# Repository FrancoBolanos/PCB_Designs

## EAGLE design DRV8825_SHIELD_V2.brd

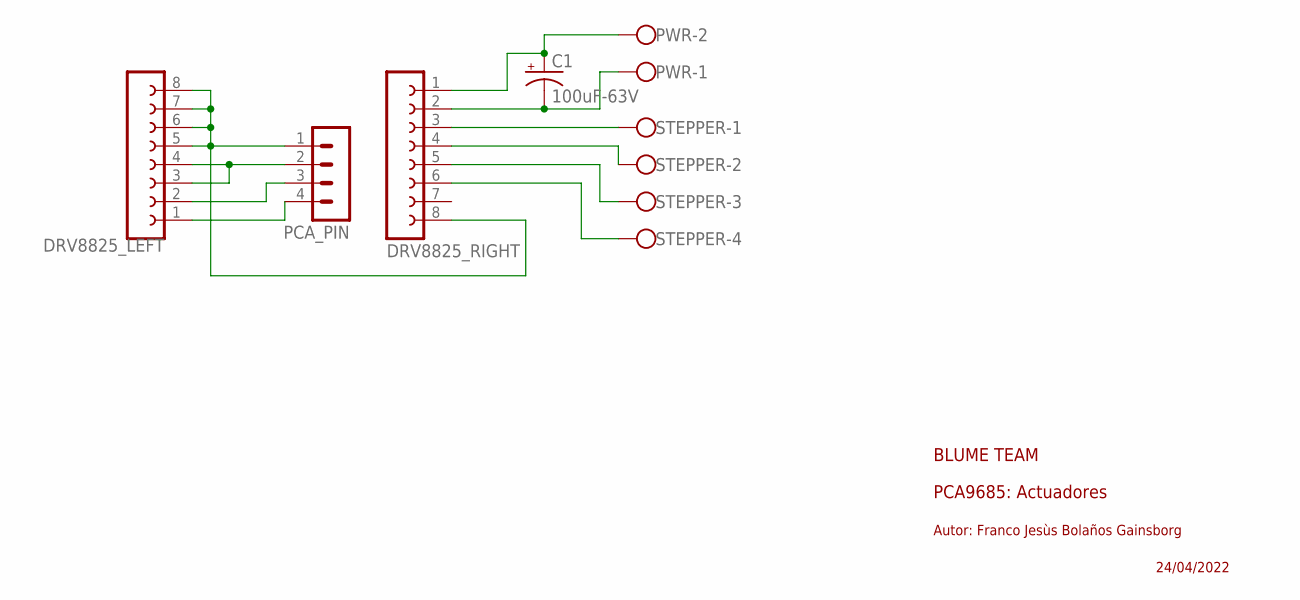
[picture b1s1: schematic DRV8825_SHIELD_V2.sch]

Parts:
C1: 100uF-63V; E5-10,5
DRV8825_LEFT, DRV8825_RIGHT: FE08-1; FE08
PCA_PIN: MA04-1
PWR: W237-102
STEPPER: W237-4

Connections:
unnamed: DRV8825_RIGHT.3, STEPPER.1
unnamed: DRV8825_RIGHT.4, STEPPER.2
unnamed: DRV8825_LEFT.1, PCA_PIN.4
unnamed: DRV8825_RIGHT.5, STEPPER.3
unnamed: C1.+, DRV8825_RIGHT.1, PWR.2
unnamed: C1.-, DRV8825_RIGHT.2, PWR.1
unnamed: DRV8825_LEFT.2, PCA_PIN.3
unnamed: DRV8825_RIGHT.6, STEPPER.4
unnamed: DRV8825_LEFT.5, DRV8825_LEFT.6, DRV8825_LEFT.7, DRV8825_LEFT.8, DRV8825_RIGHT.8, PCA_PIN.1
unnamed: DRV8825_LEFT.3, DRV8825_LEFT.4, PCA_PIN.2

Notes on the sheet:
BLUME TEAM
PCA9685: Actuadores
Autor: Franco Jesùs Bolaños Gainsborg
24/04/2022

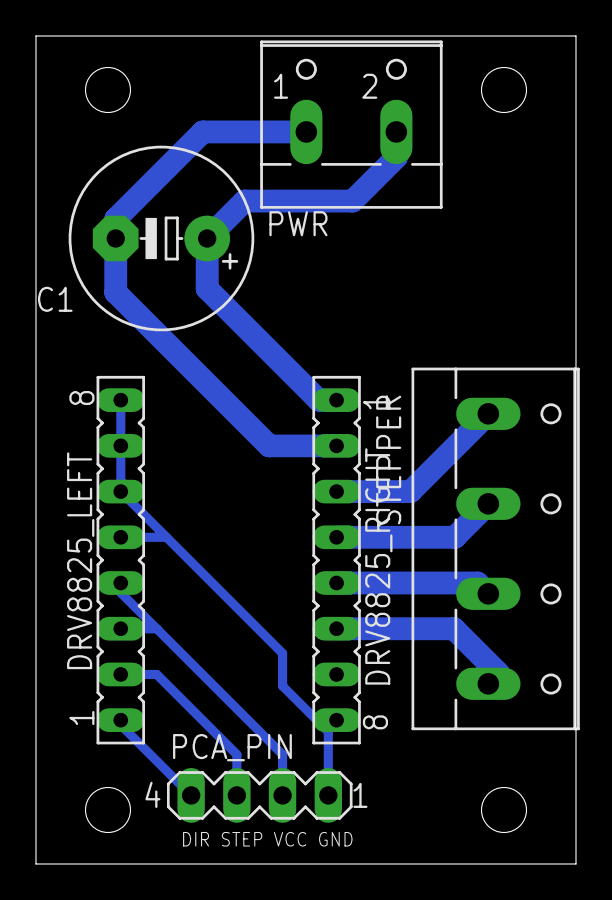
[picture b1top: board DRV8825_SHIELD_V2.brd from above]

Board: 2 copper layers, 30.0 x 46.0 mm, 6 parts (0 on the bottom side), 10 nets.

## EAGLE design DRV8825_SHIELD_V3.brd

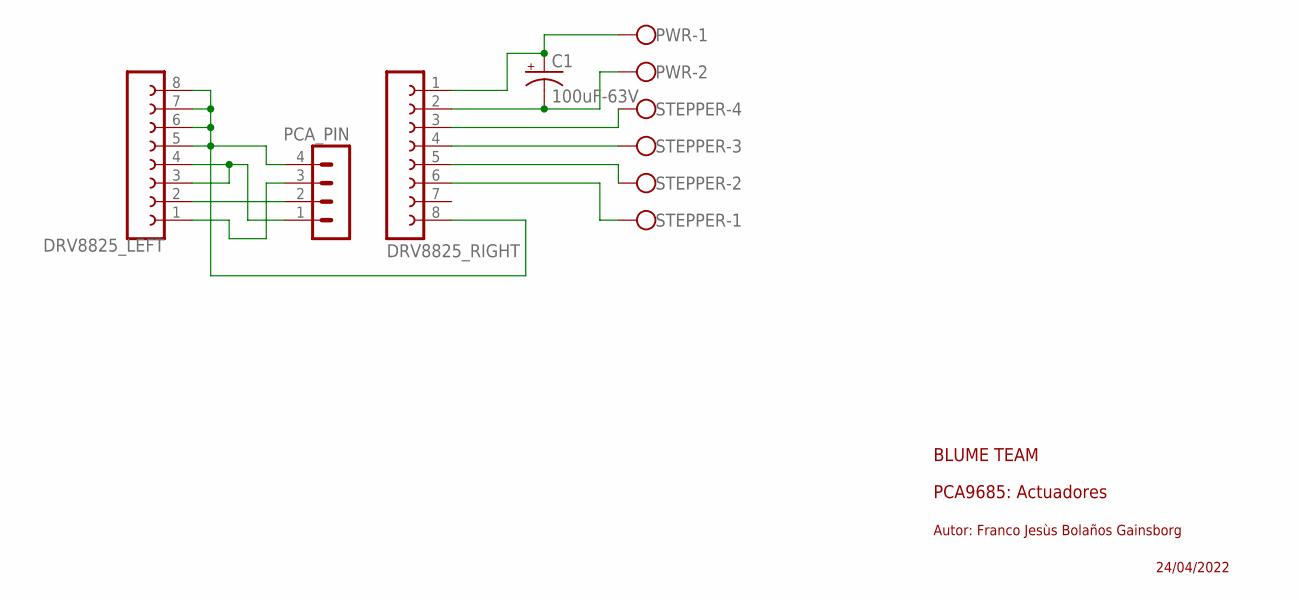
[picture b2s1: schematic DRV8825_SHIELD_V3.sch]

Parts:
C1: 100uF-63V; E5-10,5
DRV8825_LEFT, DRV8825_RIGHT: FE08-1; FE08
PCA_PIN: MA04-1
PWR: W237-102
STEPPER: W237-4

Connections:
unnamed: DRV8825_RIGHT.3, STEPPER.4
unnamed: DRV8825_RIGHT.4, STEPPER.3
unnamed: DRV8825_LEFT.2, PCA_PIN.2
unnamed: DRV8825_LEFT.1, PCA_PIN.3
unnamed: C1.+, DRV8825_RIGHT.1, PWR.1
unnamed: C1.-, DRV8825_RIGHT.2, PWR.2
unnamed: DRV8825_LEFT.3, DRV8825_LEFT.4, PCA_PIN.1
unnamed: DRV8825_RIGHT.5, STEPPER.2
unnamed: DRV8825_RIGHT.6, STEPPER.1
unnamed: DRV8825_LEFT.5, DRV8825_LEFT.6, DRV8825_LEFT.7, DRV8825_LEFT.8, DRV8825_RIGHT.8, PCA_PIN.4

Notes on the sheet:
BLUME TEAM
PCA9685: Actuadores
Autor: Franco Jesùs Bolaños Gainsborg
24/04/2022

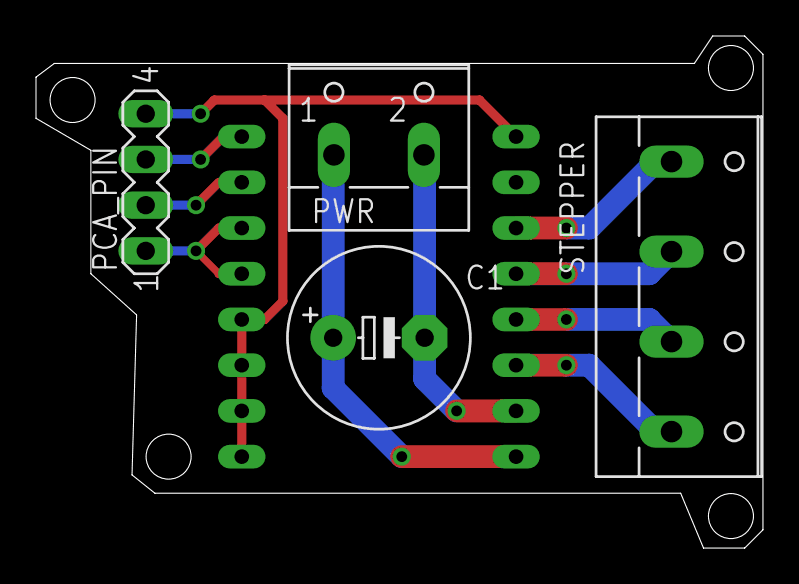
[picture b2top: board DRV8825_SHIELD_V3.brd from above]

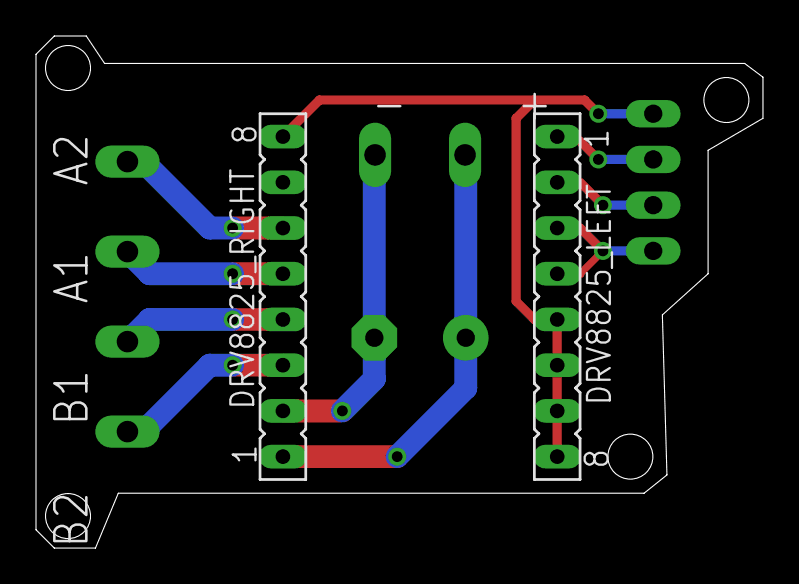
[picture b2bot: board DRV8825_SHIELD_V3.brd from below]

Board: 2 copper layers, 40.4 x 28.4 mm, 6 parts (2 on the bottom side), 10 nets.

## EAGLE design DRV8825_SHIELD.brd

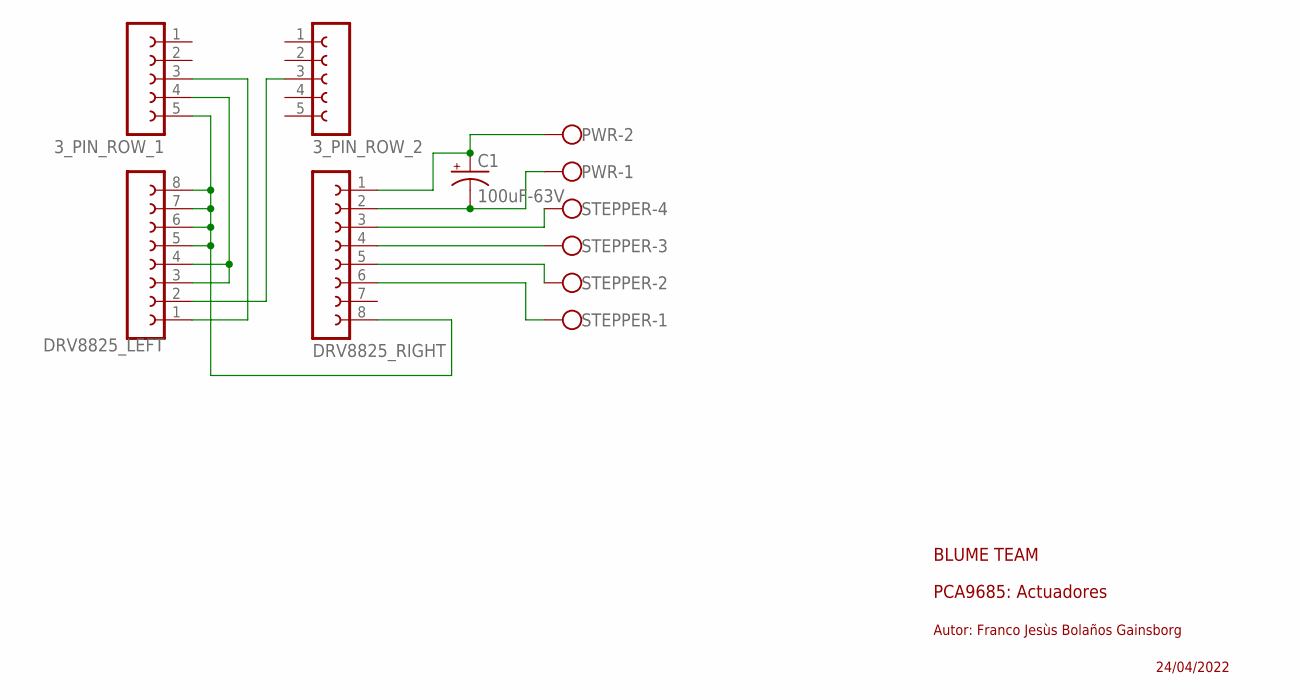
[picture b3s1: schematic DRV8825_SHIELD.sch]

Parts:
3_PIN_ROW_1, 3_PIN_ROW_2: FE05-1
C1: 100uF-63V; E5-10,5
DRV8825_LEFT, DRV8825_RIGHT: FE08-1; FE08
PWR: W237-102
STEPPER: W237-4

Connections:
unnamed: DRV8825_RIGHT.3, STEPPER.4
unnamed: 3_PIN_ROW_1.5, DRV8825_LEFT.5, DRV8825_LEFT.6, DRV8825_LEFT.7, DRV8825_LEFT.8, DRV8825_RIGHT.8
unnamed: 3_PIN_ROW_1.3, DRV8825_LEFT.1
unnamed: 3_PIN_ROW_2.3, DRV8825_LEFT.2
unnamed: C1.+, DRV8825_RIGHT.1, PWR.2
unnamed: C1.-, DRV8825_RIGHT.2, PWR.1
unnamed: DRV8825_RIGHT.4, STEPPER.3
unnamed: 3_PIN_ROW_1.4, DRV8825_LEFT.3, DRV8825_LEFT.4
unnamed: DRV8825_RIGHT.5, STEPPER.2
unnamed: DRV8825_RIGHT.6, STEPPER.1

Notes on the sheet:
BLUME TEAM
PCA9685: Actuadores
Autor: Franco Jesùs Bolaños Gainsborg
24/04/2022

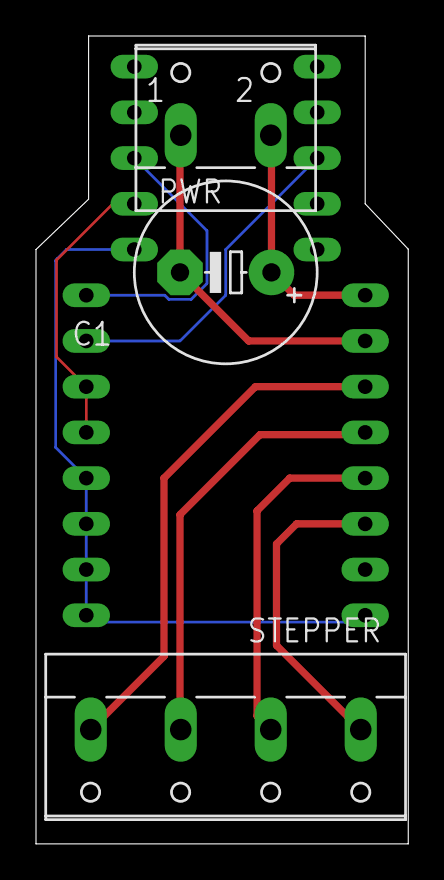
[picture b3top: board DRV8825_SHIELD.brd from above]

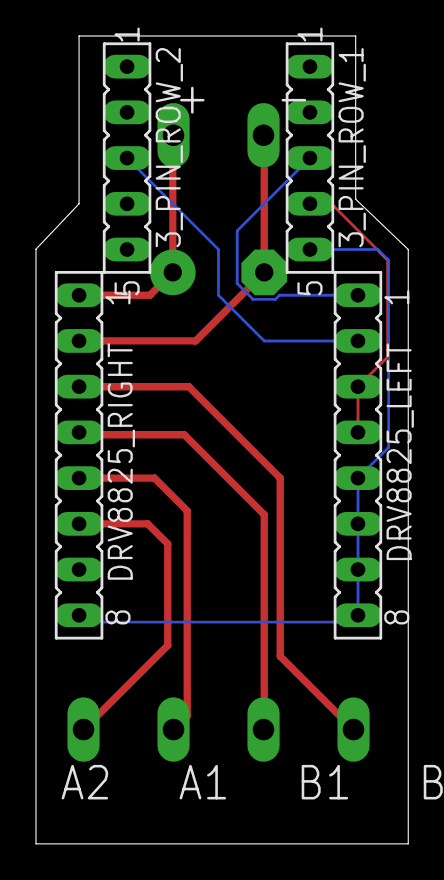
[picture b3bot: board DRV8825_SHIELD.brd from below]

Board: 2 copper layers, 20.7 x 44.9 mm, 7 parts (4 on the bottom side), 10 nets.

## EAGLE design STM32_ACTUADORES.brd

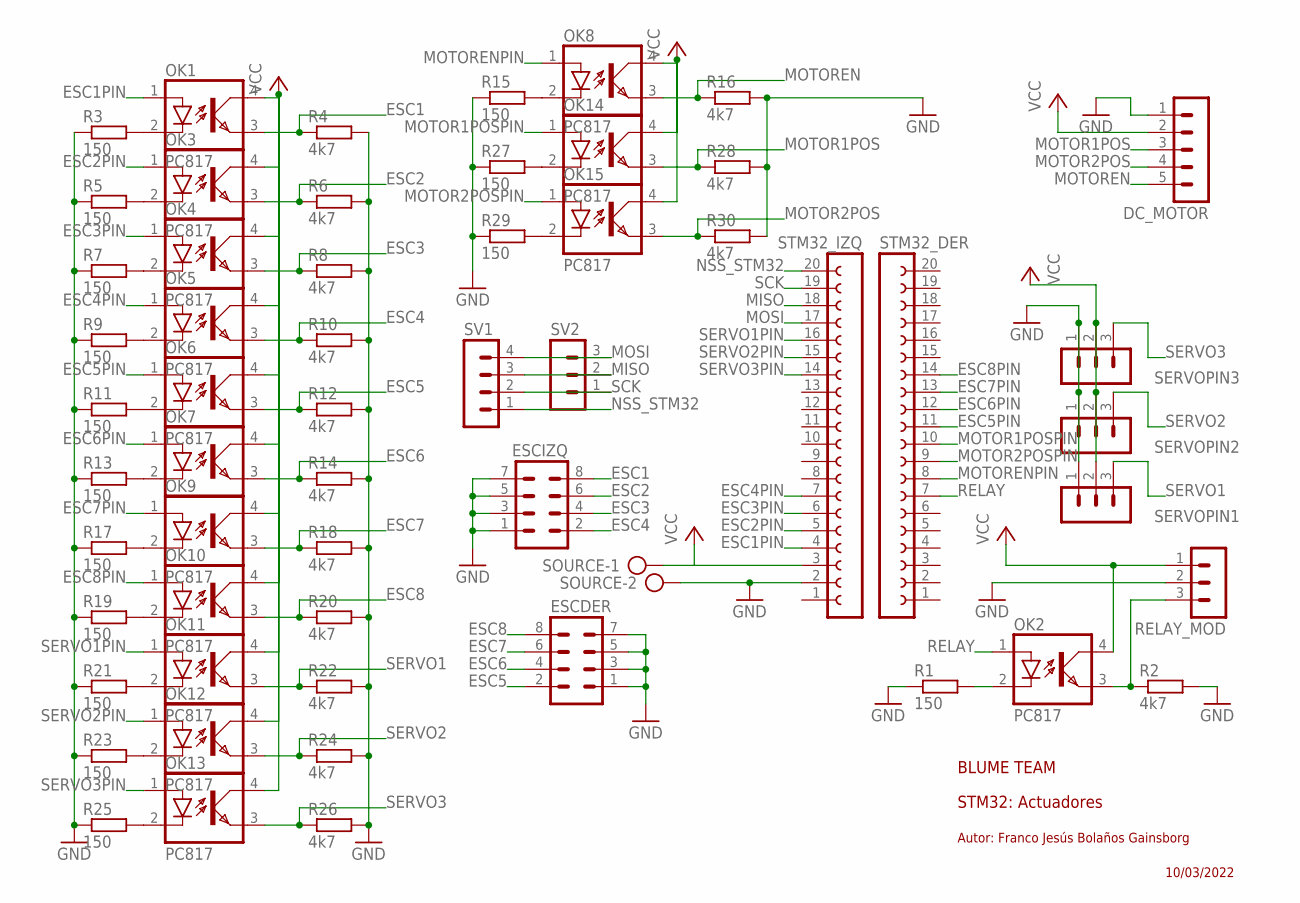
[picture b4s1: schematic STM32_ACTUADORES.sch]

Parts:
DC_MOTOR: MA05-1
ESCDER: MA04-2
ESCIZQ: MA04-2
OK1, OK2, OK3, OK4, OK5, OK6, OK7, OK8, OK9, OK10, OK11, OK12, OK13, OK14, OK15: PC817; DIL04
R1, R3, R5, R7, R9, R11, R13, R15, R17, R19, R21, R23, R25, R27, R29: 150; 0207/10
R2, R4, R6, R8, R10, R12, R14, R16, R18, R20, R22, R24, R26, R28, R30: 4k7; 0207/10
RELAY_MOD: MA03-1
SERVOPIN1, SERVOPIN2, SERVOPIN3: MA03-1
SOURCE: AK300/2
STM32_DER, STM32_IZQ: FE20-1; FE20
SV1: MA04-1
SV2: MA03-1

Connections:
ESC1: ESCIZQ.8, OK1.3 (EMIT), R4.1
ESC1PIN: OK1.1 (A), STM32_IZQ.4
ESC2: ESCIZQ.6, OK3.3 (EMIT), R6.1
ESC2PIN: OK3.1 (A), STM32_IZQ.5
ESC3: ESCIZQ.4, OK4.3 (EMIT), R8.1
ESC3PIN: OK4.1 (A), STM32_IZQ.6
ESC4: ESCIZQ.2, OK5.3 (EMIT), R10.1
ESC4PIN: OK5.1 (A), STM32_IZQ.7
ESC5: ESCDER.2, OK6.3 (EMIT), R12.1
ESC5PIN: OK6.1 (A), STM32_DER.11
ESC6: ESCDER.4, OK7.3 (EMIT), R14.1
ESC6PIN: OK7.1 (A), STM32_DER.12
ESC7: ESCDER.6, OK9.3 (EMIT), R18.1
ESC7PIN: OK9.1 (A), STM32_DER.13
ESC8: ESCDER.8, OK10.3 (EMIT), R20.1
ESC8PIN: OK10.1 (A), STM32_DER.14
GND: DC_MOTOR.1, ESCDER.1, ESCDER.3, ESCDER.5, ESCDER.7, ESCIZQ.1, ESCIZQ.3, ESCIZQ.5, ESCIZQ.7, R1.1, R2.2, R3.1, R4.2, R5.1, R6.2, R7.1, R8.2, R9.1, R10.2, R11.1, R12.2, R13.1, R14.2, R15.1, R16.2, R17.1, R18.2, R19.1, R20.2, R21.1, R22.2, R23.1, R24.2, R25.1, R26.2, R27.1, R28.2, R29.1, R30.2, RELAY_MOD.2, SERVOPIN1.1, SERVOPIN2.1, SERVOPIN3.1, SOURCE.2, STM32_IZQ.2
MISO: STM32_IZQ.18, SV1.3, SV2.2
MOSI: STM32_IZQ.17, SV1.4, SV2.3
MOTOR1POS: DC_MOTOR.3, OK14.3 (EMIT), R28.1
MOTOR1POSPIN: OK14.1 (A), STM32_DER.10
MOTOR2POS: DC_MOTOR.4, OK15.3 (EMIT), R30.1
MOTOR2POSPIN: OK15.1 (A), STM32_DER.9
MOTOREN: DC_MOTOR.5, OK8.3 (EMIT), R16.1
MOTORENPIN: OK8.1 (A), STM32_DER.8
unnamed: OK1.2 (C), R3.2
unnamed: OK2.2 (C), R1.2
unnamed: OK2.3 (EMIT), R2.1, RELAY_MOD.3
unnamed: OK8.2 (C), R15.2
unnamed: OK14.2 (C), R27.2
unnamed: OK3.2 (C), R5.2
unnamed: OK15.2 (C), R29.2
unnamed: OK13.2 (C), R25.2
unnamed: OK4.2 (C), R7.2
unnamed: OK5.2 (C), R9.2
unnamed: OK6.2 (C), R11.2
unnamed: OK7.2 (C), R13.2
unnamed: OK9.2 (C), R17.2
unnamed: OK10.2 (C), R19.2
unnamed: OK11.2 (C), R21.2
unnamed: OK12.2 (C), R23.2
NSS_STM32: STM32_IZQ.20, SV1.1
RELAY: OK2.1 (A), STM32_DER.7
SCK: STM32_IZQ.19, SV1.2, SV2.1
SERVO1: OK11.3 (EMIT), R22.1, SERVOPIN1.3
SERVO1PIN: OK11.1 (A), STM32_IZQ.16
SERVO2: OK12.3 (EMIT), R24.1, SERVOPIN2.3
SERVO2PIN: OK12.1 (A), STM32_IZQ.15
SERVO3: OK13.3 (EMIT), R26.1, SERVOPIN3.3
SERVO3PIN: OK13.1 (A), STM32_IZQ.14
VCC: DC_MOTOR.2, OK1.4 (COL), OK2.4 (COL), OK3.4 (COL), OK4.4 (COL), OK5.4 (COL), OK6.4 (COL), OK7.4 (COL), OK8.4 (COL), OK9.4 (COL), OK10.4 (COL), OK11.4 (COL), OK12.4 (COL), OK13.4 (COL), OK14.4 (COL), OK15.4 (COL), RELAY_MOD.1, SERVOPIN1.2, SERVOPIN2.2, SERVOPIN3.2, SOURCE.1, STM32_IZQ.3

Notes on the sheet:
BLUME TEAM
STM32: Actuadores
Autor: Franco Jesús Bolaños Gainsborg
10/03/2022

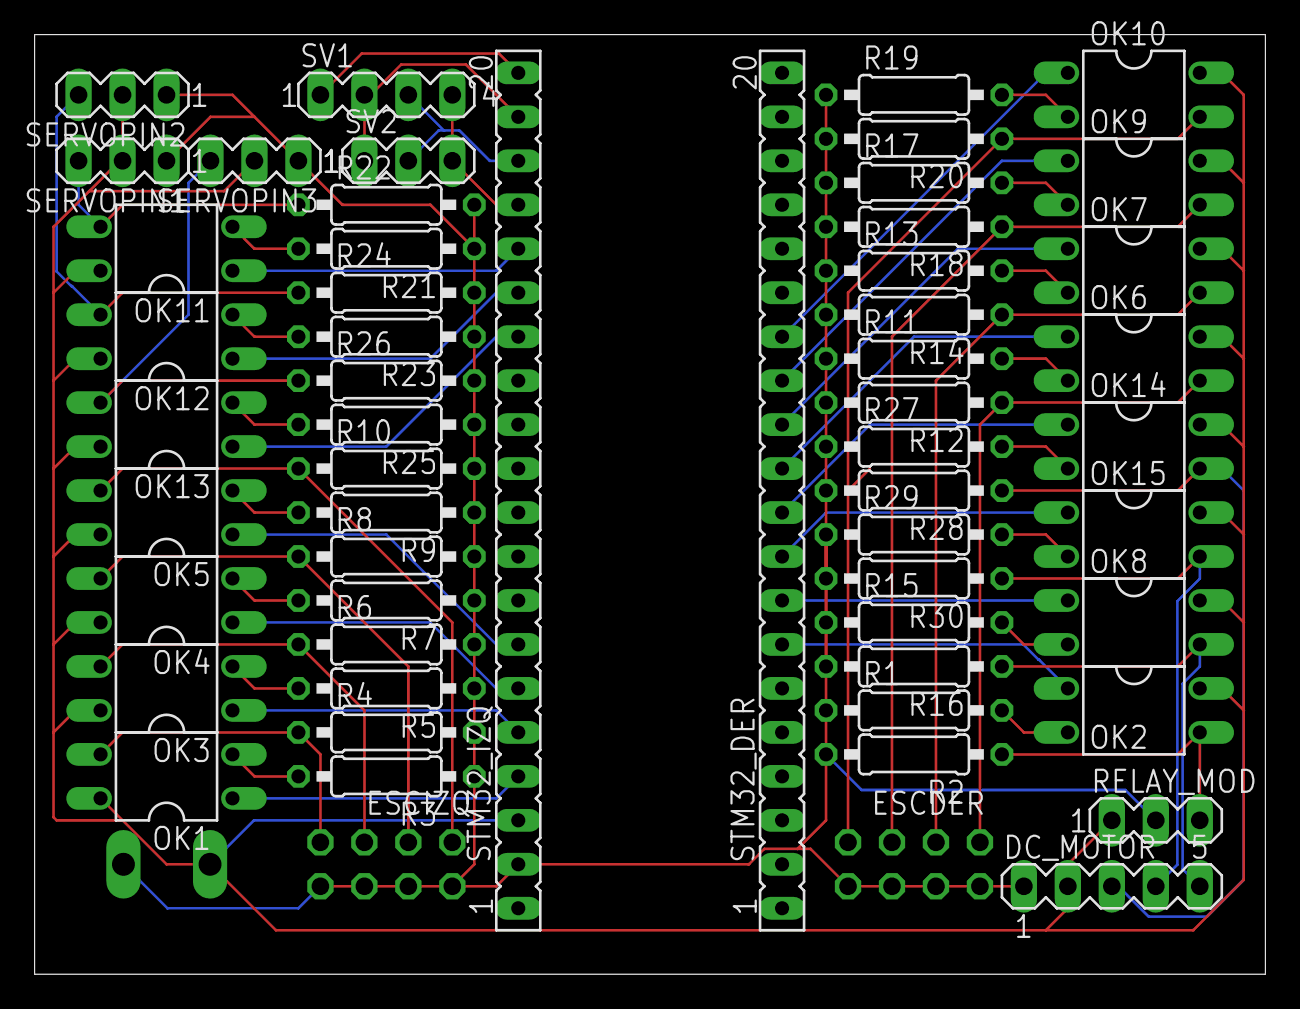
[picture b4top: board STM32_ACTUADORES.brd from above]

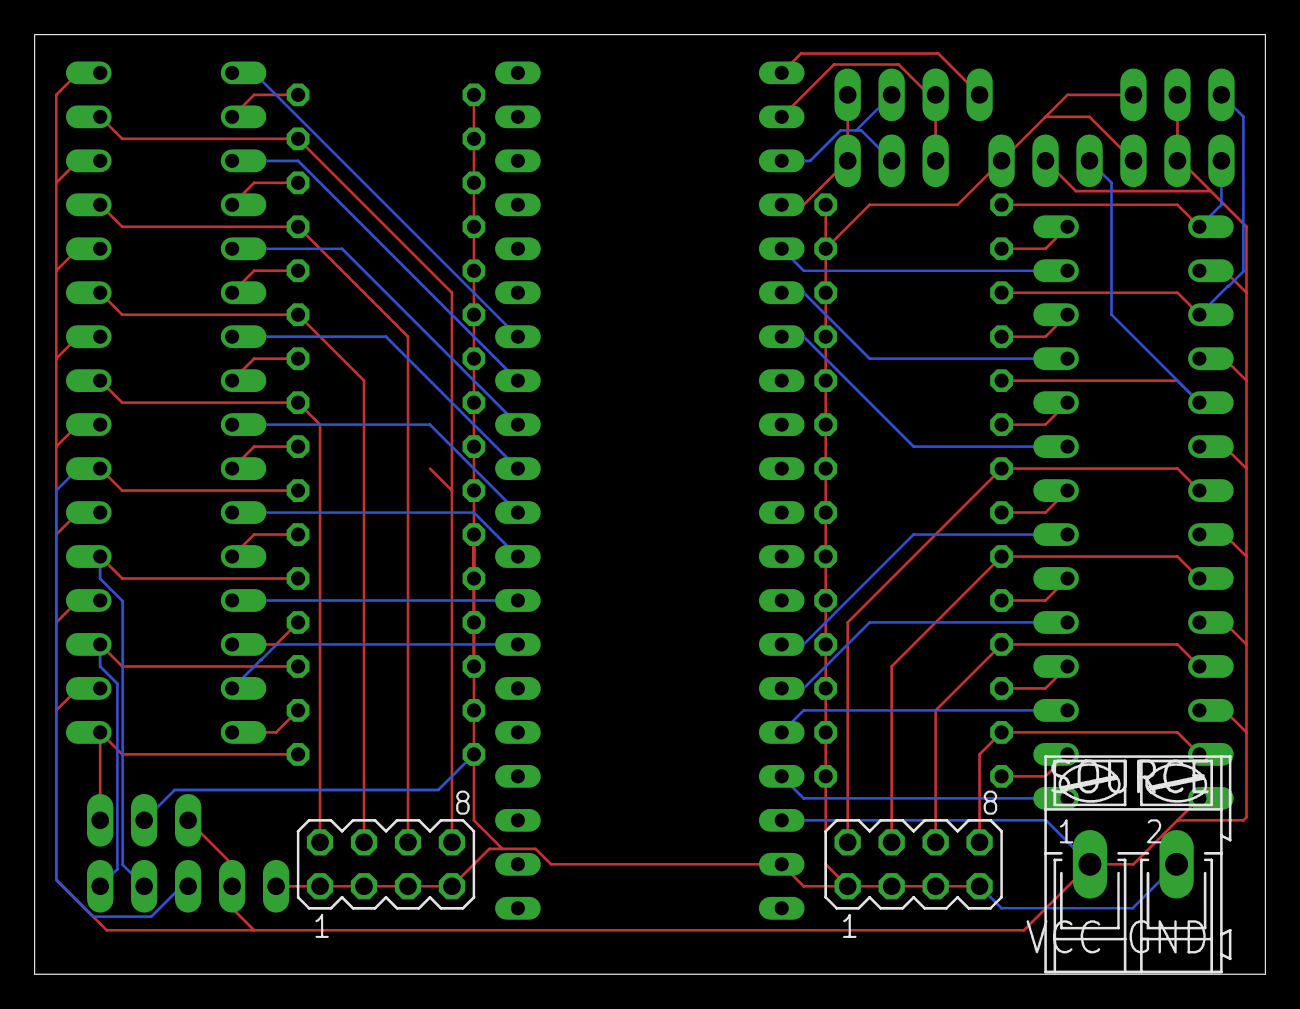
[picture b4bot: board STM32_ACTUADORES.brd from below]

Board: 2 copper layers, 71.1 x 54.3 mm, 57 parts (3 on the bottom side), 51 nets.
